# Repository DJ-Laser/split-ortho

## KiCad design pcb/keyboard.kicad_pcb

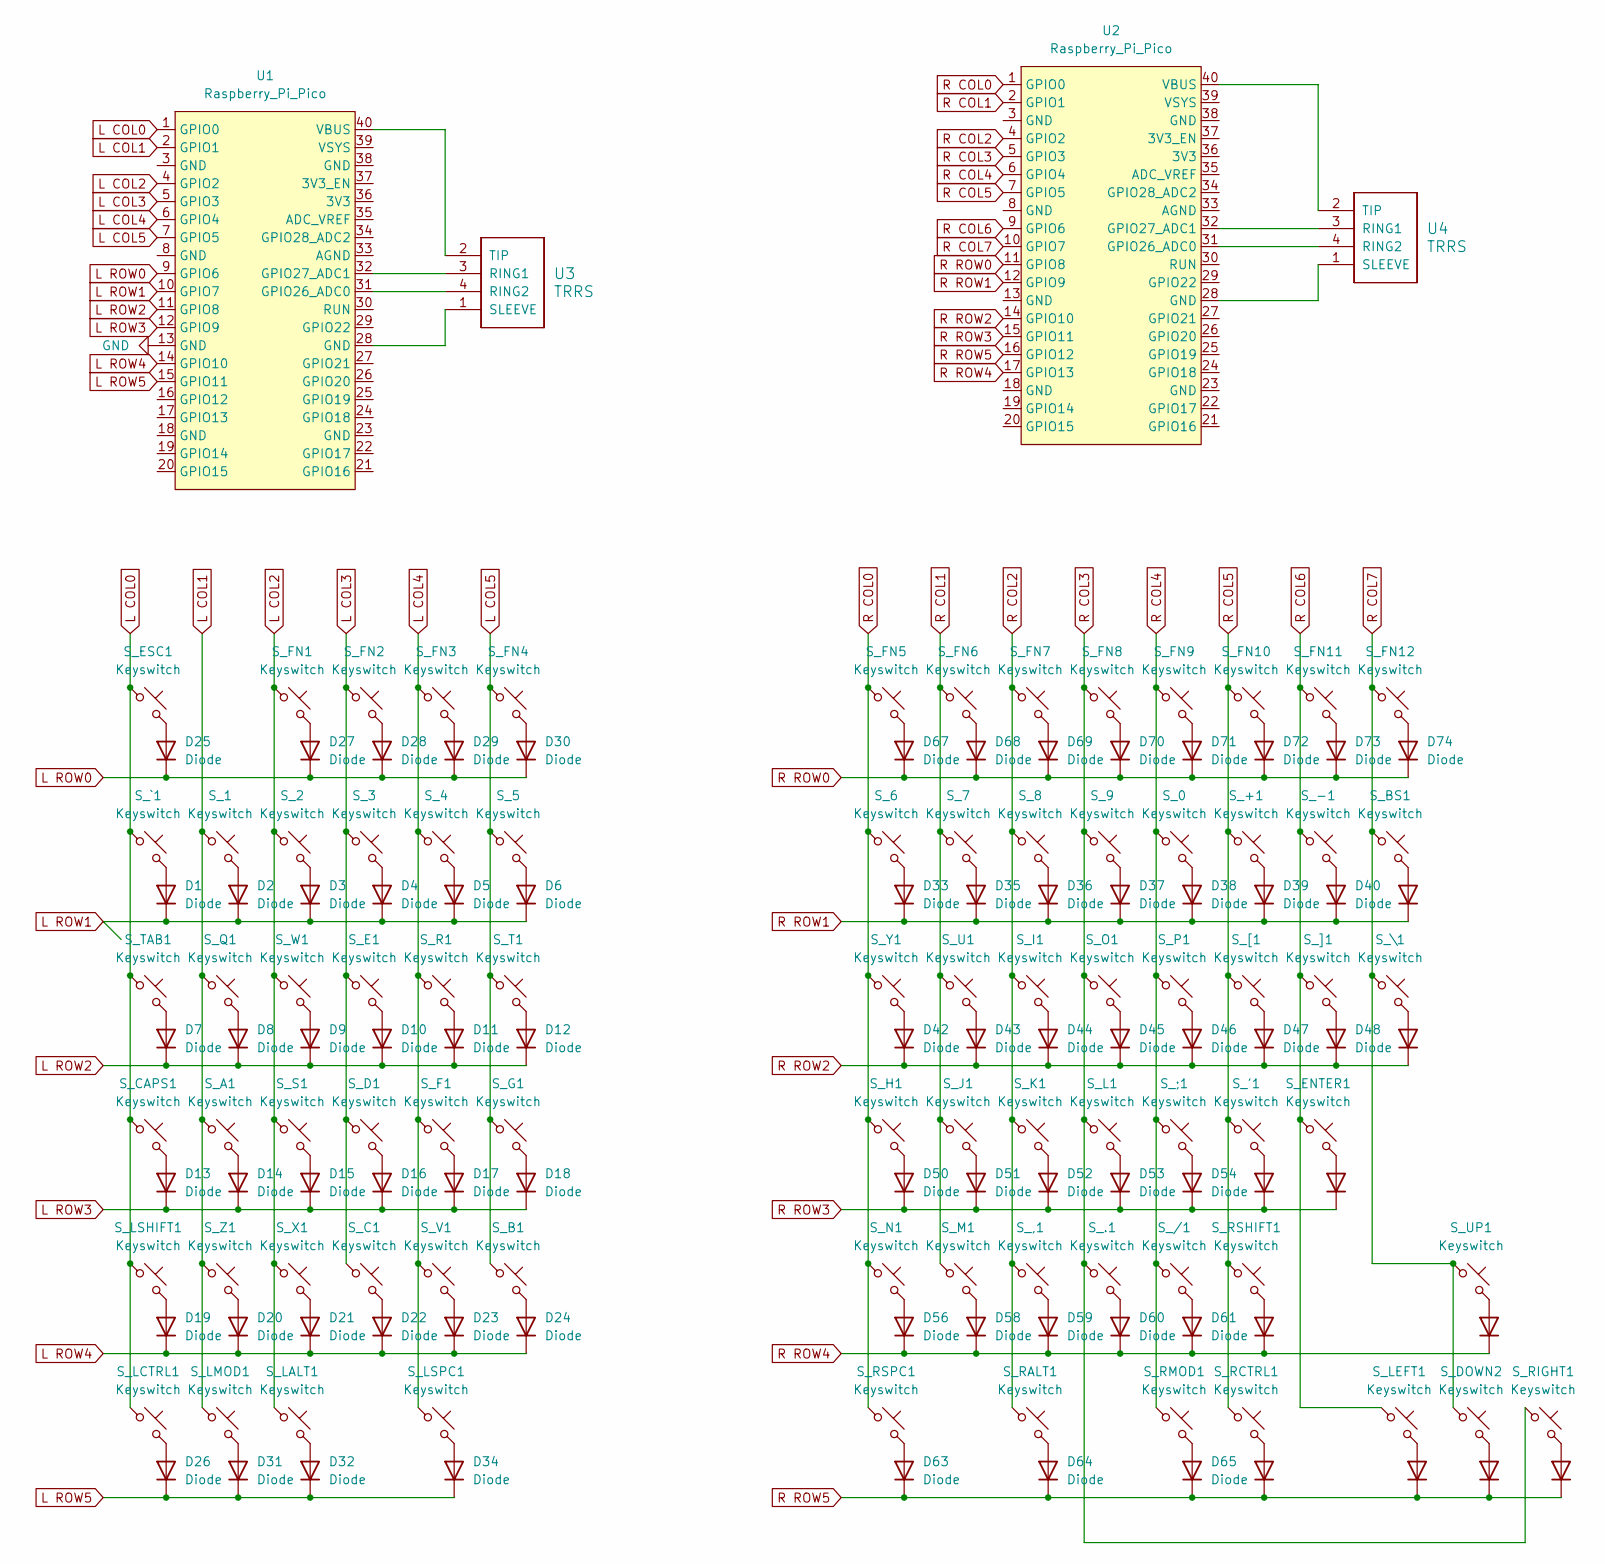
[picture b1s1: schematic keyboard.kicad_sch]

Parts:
D1, D2, D3, D4, D5, D6, D7, D8, D9, D10, D11, D12, D13, D14, D15, D16, D17, D18, D19, D20, D21, D22, D23, D24, D25, D26, D27, D28, D29, D30, D31, D32, D33, D34, D35, D36, D37, D38, D39, D40, D41, D42, D43, D44, D45, D46, D47, D48, D49, D50, D51, D52, D53, D54, D55, D56, D57, D58, D59, D60, D61, D62, D63, D64, D65, D66, D67, D68, D69, D70, D71, D72, D73, D74, D75, D76, D77, D78: Diode; D_DO-35_SOD27_P7.62mm_Horizontal
S_0, S_1, S_2, S_3, S_4, S_5, S_6, S_7, S_8, S_9, S_.1: Keyswitch; Hotswap_MX_1.00u
S_'1: Keyswitch; Hotswap_MX_1.00u
S_+1: Keyswitch; Hotswap_MX_1.00u
S_,1: Keyswitch; Hotswap_MX_1.00u
S_-1: Keyswitch; Hotswap_MX_1.00u
S_/1: Keyswitch; Hotswap_MX_1.00u
S_;1: Keyswitch; Hotswap_MX_1.00u
S_A1: Keyswitch; Hotswap_MX_1.00u
S_B1: Keyswitch; Hotswap_MX_1.00u
S_BS1: Keyswitch; Hotswap_MX_1.50u
S_C1: Keyswitch; Hotswap_MX_1.00u
S_CAPS1: Keyswitch; Hotswap_MX_1.50u
S_D1: Keyswitch; Hotswap_MX_1.00u
S_DOWN2: Keyswitch; Hotswap_MX_1.00u
S_E1: Keyswitch; Hotswap_MX_1.00u
S_ENTER1: Keyswitch; Hotswap_MX_2.00u
S_ESC1: Keyswitch; Hotswap_MX_2.00u
S_F1: Keyswitch; Hotswap_MX_1.00u
S_FN1, S_FN2, S_FN3, S_FN4, S_FN5, S_FN6, S_FN7, S_FN8, S_FN9, S_FN10, S_FN11, S_FN12: Keyswitch; Hotswap_MX_1.00u
S_G1: Keyswitch; Hotswap_MX_1.00u
S_H1: Keyswitch; Hotswap_MX_1.00u
S_I1: Keyswitch; Hotswap_MX_1.00u
S_J1: Keyswitch; Hotswap_MX_1.00u
S_K1: Keyswitch; Hotswap_MX_1.00u
S_L1: Keyswitch; Hotswap_MX_1.00u
S_LALT1: Keyswitch; Hotswap_MX_1.25u
S_LCTRL1: Keyswitch; Hotswap_MX_1.50u
S_LEFT1: Keyswitch; Hotswap_MX_1.00u
S_LMOD1: Keyswitch; Hotswap_MX_1.25u
S_LSHIFT1: Keyswitch; Hotswap_MX_1.50u
S_LSPC1: Keyswitch; Hotswap_MX_2.50u
S_M1: Keyswitch; Hotswap_MX_1.00u
S_N1: Keyswitch; Hotswap_MX_1.00u
S_O1: Keyswitch; Hotswap_MX_1.00u
S_P1: Keyswitch; Hotswap_MX_1.00u
S_Q1: Keyswitch; Hotswap_MX_1.00u
S_R1: Keyswitch; Hotswap_MX_1.00u
S_RALT1: Keyswitch; Hotswap_MX_1.25u
S_RCTRL1: Keyswitch; Hotswap_MX_1.25u
S_RIGHT1: Keyswitch; Hotswap_MX_1.00u
S_RMOD1: Keyswitch; Hotswap_MX_1.25u
S_RSHIFT1: Keyswitch; Hotswap_MX_2.00u
S_RSPC1: Keyswitch; Hotswap_MX_2.50u
S_S1: Keyswitch; Hotswap_MX_1.00u
S_T1: Keyswitch; Hotswap_MX_1.00u
S_TAB1: Keyswitch; Hotswap_MX_1.50u
S_U1: Keyswitch; Hotswap_MX_1.00u
S_UP1: Keyswitch; Hotswap_MX_1.00u
S_V1: Keyswitch; Hotswap_MX_1.00u
S_W1: Keyswitch; Hotswap_MX_1.00u
S_X1: Keyswitch; Hotswap_MX_1.00u
S_Y1: Keyswitch; Hotswap_MX_1.00u
S_Z1: Keyswitch; Hotswap_MX_1.00u
S_[1: Keyswitch; Hotswap_MX_1.00u
S_\1: Keyswitch; Hotswap_MX_1.50u
S_]1: Keyswitch; Hotswap_MX_1.00u
S_`1: Keyswitch; Hotswap_MX_1.50u
U1, U2: Raspberry_Pi_Pico
U3, U4: TRRS; TRRS_PJ-320A

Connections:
GND: U1.13 (GND)
L COL0: S_CAPS1.1, S_ESC1.1, S_LCTRL1.1, S_LSHIFT1.1, S_TAB1.1, S_`1.1, U1.1 (GPIO0)
L COL1: S_1.1, S_A1.1, S_LMOD1.1, S_Q1.1, S_Z1.1, U1.2 (GPIO1)
L COL2: S_2.1, S_FN1.1, S_LALT1.1, S_S1.1, S_W1.1, S_X1.1, U1.4 (GPIO2)
L COL3: S_3.1, S_C1.1, S_D1.1, S_E1.1, S_FN2.1, U1.5 (GPIO3)
L COL4: S_4.1, S_F1.1, S_FN3.1, S_LSPC1.1, S_R1.1, S_V1.1, U1.6 (GPIO4)
L COL5: S_5.1, S_B1.1, S_FN4.1, S_G1.1, S_T1.1, U1.7 (GPIO5)
L ROW0: D25.1 (K), D27.1 (K), D28.1 (K), D29.1 (K), D30.1 (K), U1.9 (GPIO6)
L ROW1: D1.1 (K), D2.1 (K), D3.1 (K), D4.1 (K), D5.1 (K), D6.1 (K), U1.10 (GPIO7)
L ROW2: D7.1 (K), D8.1 (K), D9.1 (K), D10.1 (K), D11.1 (K), D12.1 (K), U1.11 (GPIO8)
L ROW3: D13.1 (K), D14.1 (K), D15.1 (K), D16.1 (K), D17.1 (K), D18.1 (K), U1.12 (GPIO9)
L ROW4: D19.1 (K), D20.1 (K), D21.1 (K), D22.1 (K), D23.1 (K), D24.1 (K), U1.14 (GPIO10)
L ROW5: D26.1 (K), D31.1 (K), D32.1 (K), D34.1 (K), U1.15 (GPIO11)
unnamed: D1.2 (A), S_`1.2
unnamed: D2.2 (A), S_1.2
unnamed: D3.2 (A), S_2.2
unnamed: D4.2 (A), S_3.2
unnamed: D5.2 (A), S_4.2
unnamed: D6.2 (A), S_5.2
unnamed: D7.2 (A), S_TAB1.2
unnamed: D8.2 (A), S_Q1.2
unnamed: D9.2 (A), S_W1.2
unnamed: D10.2 (A), S_E1.2
unnamed: D11.2 (A), S_R1.2
unnamed: D12.2 (A), S_T1.2
unnamed: D13.2 (A), S_CAPS1.2
unnamed: D14.2 (A), S_A1.2
unnamed: D15.2 (A), S_S1.2
unnamed: D16.2 (A), S_D1.2
unnamed: D17.2 (A), S_F1.2
unnamed: D18.2 (A), S_G1.2
unnamed: D19.2 (A), S_LSHIFT1.2
unnamed: D20.2 (A), S_Z1.2
unnamed: D21.2 (A), S_X1.2
unnamed: D22.2 (A), S_C1.2
unnamed: D23.2 (A), S_V1.2
unnamed: D24.2 (A), S_B1.2
unnamed: D25.2 (A), S_ESC1.2
unnamed: D26.2 (A), S_LCTRL1.2
unnamed: D27.2 (A), S_FN1.2
unnamed: D28.2 (A), S_FN2.2
unnamed: D29.2 (A), S_FN3.2
unnamed: D30.2 (A), S_FN4.2
unnamed: D31.2 (A), S_LMOD1.2
unnamed: D32.2 (A), S_LALT1.2
unnamed: D33.2 (A), S_6.2
unnamed: D34.2 (A), S_LSPC1.2
unnamed: D35.2 (A), S_7.2
unnamed: D36.2 (A), S_8.2
unnamed: D37.2 (A), S_9.2
unnamed: D38.2 (A), S_0.2
unnamed: D39.2 (A), S_+1.2
unnamed: D40.2 (A), S_-1.2
unnamed: D41.2 (A), S_BS1.2
unnamed: D42.2 (A), S_Y1.2
unnamed: D43.2 (A), S_U1.2
unnamed: D44.2 (A), S_I1.2
unnamed: D45.2 (A), S_O1.2
unnamed: D46.2 (A), S_P1.2
unnamed: D47.2 (A), S_[1.2
unnamed: D48.2 (A), S_]1.2
unnamed: D49.2 (A), S_\1.2
unnamed: D50.2 (A), S_H1.2
unnamed: D51.2 (A), S_J1.2
unnamed: D52.2 (A), S_K1.2
unnamed: D53.2 (A), S_L1.2
unnamed: D54.2 (A), S_;1.2
unnamed: D55.2 (A), S_'1.2
unnamed: D56.2 (A), S_N1.2
unnamed: D57.2 (A), S_ENTER1.2
unnamed: D58.2 (A), S_M1.2
unnamed: D59.2 (A), S_,1.2
unnamed: D60.2 (A), S_.1.2
unnamed: D61.2 (A), S_/1.2
unnamed: D62.2 (A), S_RSHIFT1.2
unnamed: D63.2 (A), S_RSPC1.2
unnamed: D64.2 (A), S_RALT1.2
unnamed: D65.2 (A), S_RMOD1.2
unnamed: D66.2 (A), S_RCTRL1.2
unnamed: D67.2 (A), S_FN5.2
unnamed: D68.2 (A), S_FN6.2
unnamed: D69.2 (A), S_FN7.2
unnamed: D70.2 (A), S_FN8.2
unnamed: D71.2 (A), S_FN9.2
unnamed: D72.2 (A), S_FN10.2
unnamed: D73.2 (A), S_FN11.2
unnamed: D74.2 (A), S_FN12.2
unnamed: D75.2 (A), S_LEFT1.2
unnamed: D76.2 (A), S_DOWN2.2
unnamed: D77.2 (A), S_RIGHT1.2
unnamed: D78.2 (A), S_UP1.2
unnamed: U1.31 (GPIO26_ADC0), U3.4 (RING2)
unnamed: U1.32 (GPIO27_ADC1), U3.3 (RING1)
unnamed: U1.40 (VBUS), U3.2 (TIP)
unnamed: U2.31 (GPIO26_ADC0), U4.4 (RING2)
unnamed: U2.32 (GPIO27_ADC1), U4.3 (RING1)
unnamed: U2.40 (VBUS), U4.2 (TIP)
unnamed: U1.28 (GND), U3.1 (SLEEVE)
unnamed: U2.28 (GND), U4.1 (SLEEVE)
R COL0: S_6.1, S_FN5.1, S_H1.1, S_N1.1, S_RSPC1.1, S_Y1.1, U2.1 (GPIO0)
R COL1: S_7.1, S_FN6.1, S_J1.1, S_M1.1, S_U1.1, U2.2 (GPIO1)
R COL2: S_8.1, S_,1.1, S_FN7.1, S_I1.1, S_K1.1, S_RALT1.1, U2.4 (GPIO2)
R COL3: S_9.1, S_.1.1, S_FN8.1, S_L1.1, S_O1.1, S_RIGHT1.1, U2.5 (GPIO3)
R COL4: S_0.1, S_/1.1, S_;1.1, S_FN9.1, S_P1.1, S_RMOD1.1, U2.6 (GPIO4)
R COL5: S_'1.1, S_+1.1, S_FN10.1, S_RCTRL1.1, S_RSHIFT1.1, S_[1.1, U2.7 (GPIO5)
R COL6: S_-1.1, S_ENTER1.1, S_FN11.1, S_LEFT1.1, S_]1.1, U2.9 (GPIO6)
R COL7: S_BS1.1, S_DOWN2.1, S_FN12.1, S_UP1.1, S_\1.1, U2.10 (GPIO7)
R ROW0: D67.1 (K), D68.1 (K), D69.1 (K), D70.1 (K), D71.1 (K), D72.1 (K), D73.1 (K), D74.1 (K), U2.11 (GPIO8)
R ROW1: D33.1 (K), D35.1 (K), D36.1 (K), D37.1 (K), D38.1 (K), D39.1 (K), D40.1 (K), D41.1 (K), U2.12 (GPIO9)
R ROW2: D42.1 (K), D43.1 (K), D44.1 (K), D45.1 (K), D46.1 (K), D47.1 (K), D48.1 (K), D49.1 (K), U2.14 (GPIO10)
R ROW3: D50.1 (K), D51.1 (K), D52.1 (K), D53.1 (K), D54.1 (K), D55.1 (K), D57.1 (K), U2.15 (GPIO11)
R ROW4: D56.1 (K), D58.1 (K), D59.1 (K), D60.1 (K), D61.1 (K), D62.1 (K), D78.1 (K), U2.17 (GPIO13)
R ROW5: D63.1 (K), D64.1 (K), D65.1 (K), D66.1 (K), D75.1 (K), D76.1 (K), D77.1 (K), U2.16 (GPIO12)

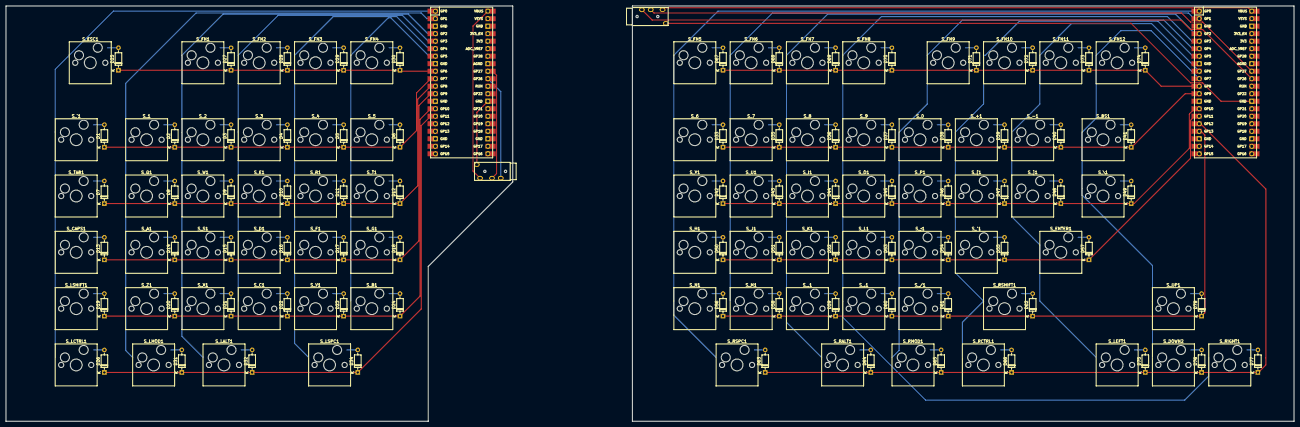
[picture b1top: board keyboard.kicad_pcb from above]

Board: 2 copper layers, 435.8 x 140.5 mm, 160 parts (0 on the bottom side), 112 nets.

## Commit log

2025-02-26 pcb revision 1 (speedrun so its a bit jank :| )
2025-02-26 Create LICENSE
2025-02-26 forgot to save
